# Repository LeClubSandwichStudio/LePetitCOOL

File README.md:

# Le Petit COOL
The Open Source DIY Greenhouse Kit for Makers

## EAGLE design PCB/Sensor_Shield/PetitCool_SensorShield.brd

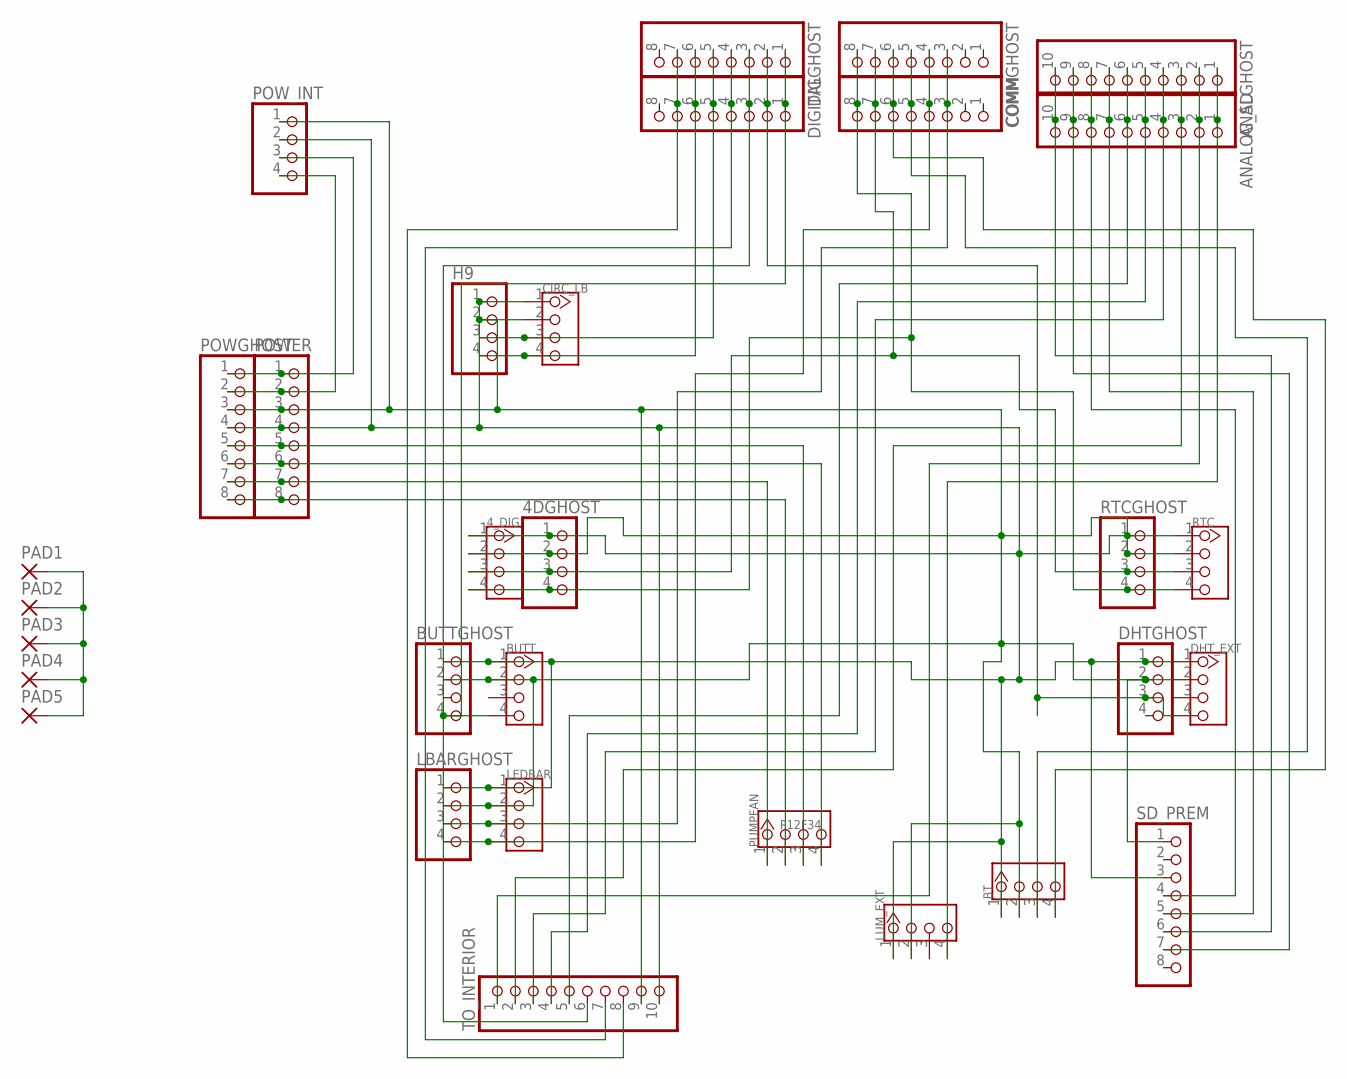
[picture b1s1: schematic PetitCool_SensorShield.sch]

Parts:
4DGHOST: PINHD-1X4; 1X04
4_DIG: TWIG-4P-2.0-2.0; 4P-2.0
ANALGHOST: PINHD-1X10; 1X10
ANALOG_SD: PINHD-1X10; 1X10
BT: TWIG-4P-2.0-2.0; 4P-2.0
BUTT: TWIG-4P-2.0-2.0; 4P-2.0
BUTTGHOST: PINHD-1X4; 1X04
CIRC_LB: TWIG-4P-2.0-2.0; 4P-2.0
COMM: PINHD-1X8; 1X08
COMMGHOST: PINHD-1X8; 1X08
DHTGHOST: PINHD-1X4; 1X04
DHT_EXT: TWIG-4P-2.0-2.0; 4P-2.0
DIGGHOST: PINHD-1X8; 1X08
DIGITAL: PINHD-1X8; 1X08
H9: PINHD-1X4; 1X04
LBARGHOST: PINHD-1X4; 1X04
LEDBAR: TWIG-4P-2.0-2.0; 4P-2.0
LUM_EXT: TWIG-4P-2.0-2.0; 4P-2.0
PAD1, PAD2, PAD3, PAD4, PAD5: 2,15/1,0
POWER: PINHD-1X8; 1X08
POWGHOST: PINHD-1X8; 1X08
POW_INT: PINHD-1X4; 1X04
PUMPFAN: P12F34; 4P-2.0
RTC: TWIG-4P-2.0-2.0; 4P-2.0
RTCGHOST: PINHD-1X4; 1X04
SD_PREM: PINHD-1X8; 1X08
TO_INTERIOR: PINHD-1X10; 1X10

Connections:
+5V: 4DGHOST.2, 4_DIG.2, BT.2, BUTT.2, BUTTGHOST.2, CIRC_LB.2, DHTGHOST.2, DHT_EXT.2, H9.2, LBARGHOST.2, LEDBAR.2, LUM_EXT.2, POWER.3, POWGHOST.3, POW_INT.1, RTC.2, RTCGHOST.2, SD_PREM.1, TO_INTERIOR.9
+12V: POWER.1, POWGHOST.1, POW_INT.3
+FANS: POWER.5, POWGHOST.5, PUMPFAN.3
+PUMP: POWER.7, POWGHOST.7, PUMPFAN.1
A_PTSHIELD(A14): ANALGHOST.6, ANALOG_SD.6, TO_INTERIOR.5
BT_RX: BT.3, COMM.5, COMMGHOST.5
BT_TX: BT.4, COMM.6, COMMGHOST.6
BUTT(32): BUTT.4, BUTTGHOST.4, DIGGHOST.1, DIGITAL.1
CLB_CLK(42): CIRC_LB.4, DIGGHOST.6, DIGITAL.6, H9.4
CLB_DATA(40): CIRC_LB.3, DIGGHOST.5, DIGITAL.5, H9.3
DHT_EXT(34): DHTGHOST.3, DHT_EXT.4, DIGGHOST.2, DIGITAL.2
DHT_INT(36): DIGGHOST.3, DIGITAL.3, TO_INTERIOR.6
D_PTSHIELD(44): DIGGHOST.7, DIGITAL.7, TO_INTERIOR.8
GND_5V: 4DGHOST.1, 4_DIG.1, BT.1, BUTT.1, BUTTGHOST.1, CIRC_LB.1, DHTGHOST.1, DHT_EXT.1, H9.1, LBARGHOST.1, LEDBAR.1, LUM_EXT.1, PAD1.1, PAD2.1, PAD3.1, PAD4.1, PAD5.1, POWER.4, POWGHOST.4, POW_INT.2, RTC.1, RTCGHOST.1, SD_PREM.3, TO_INTERIOR.10
GND_12V: POWER.2, POWGHOST.2, POW_INT.4
GND_FANS: POWER.6, POWGHOST.6, PUMPFAN.4
GND_PUMP: POWER.8, POWGHOST.8, PUMPFAN.2
LEDBAR_RX: COMM.3, COMMGHOST.3, LBARGHOST.3, LEDBAR.3
LEDBAR_TX: COMM.4, COMMGHOST.4, LBARGHOST.4, LEDBAR.4
LUM_EXT(A9): ANALGHOST.1, ANALOG_SD.1, LUM_EXT.4
LUM_INT(A10): ANALGHOST.2, ANALOG_SD.2, TO_INTERIOR.1
MOIST_1(A11): ANALGHOST.3, ANALOG_SD.3, TO_INTERIOR.2
MOIST_2(A12): ANALGHOST.4, ANALOG_SD.4, TO_INTERIOR.3
MOIST_3(A13): ANALGHOST.5, ANALOG_SD.5, TO_INTERIOR.4
PROXI_US(38): DIGGHOST.4, DIGITAL.4, TO_INTERIOR.7
SCL: 4DGHOST.4, 4_DIG.4, COMM.8, COMMGHOST.8, RTC.4, RTCGHOST.4
SDA: 4DGHOST.3, 4_DIG.3, COMM.7, COMMGHOST.7, RTC.3, RTCGHOST.3
SD_CLK(52): ANALGHOST.8, ANALOG_SD.8, SD_PREM.4
SD_CS(53): ANALGHOST.9, ANALOG_SD.9, SD_PREM.7
SD_DI(51): ANALGHOST.10, ANALOG_SD.10, SD_PREM.6
SD_DO(50): ANALGHOST.7, ANALOG_SD.7, SD_PREM.5

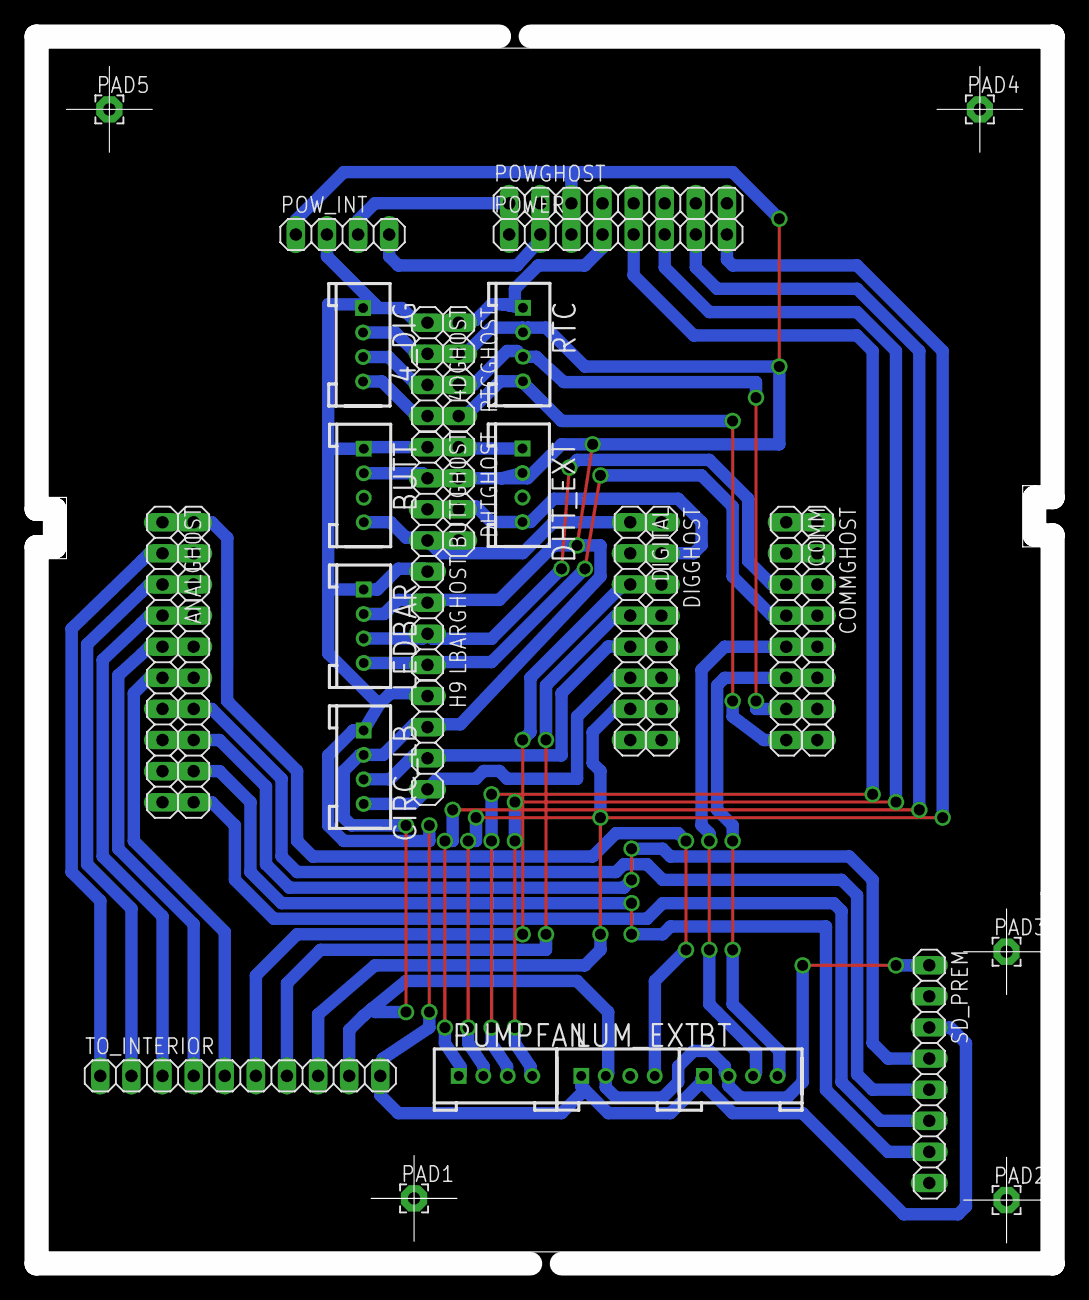
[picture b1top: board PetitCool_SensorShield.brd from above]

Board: 2 copper layers, 83.0 x 100.2 mm, 31 parts (0 on the bottom side), 31 nets.

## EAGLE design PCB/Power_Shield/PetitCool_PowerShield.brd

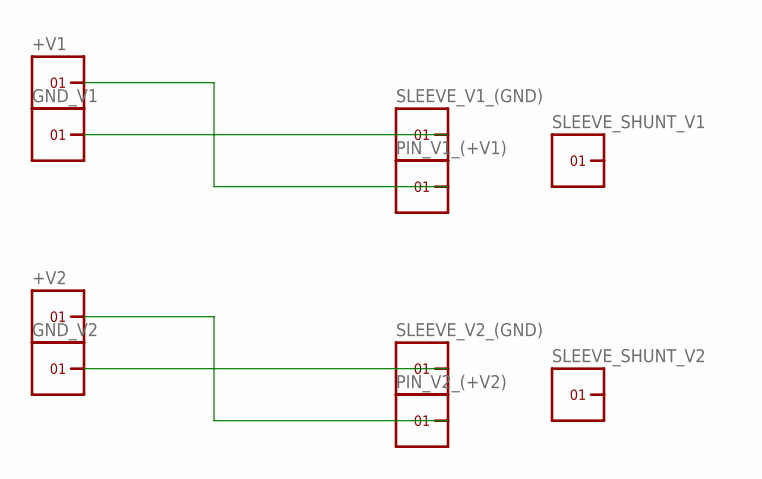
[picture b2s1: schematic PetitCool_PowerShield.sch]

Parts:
+V1, +V2: 1X1
GND_V1, GND_V2: 1X1
PIN_V1_(+V1), PIN_V2_(+V2): 1X1
SLEEVE_SHUNT_V1, SLEEVE_SHUNT_V2: 1X1
SLEEVE_V1_(GND), SLEEVE_V2_(GND): 1X1

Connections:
+V1: +V1.1, PIN_V1_(+V1).1
+V2: +V2.1, PIN_V2_(+V2).1
GND_V1: GND_V1.1, SLEEVE_V1_(GND).1
GND_V2: GND_V2.1, SLEEVE_V2_(GND).1

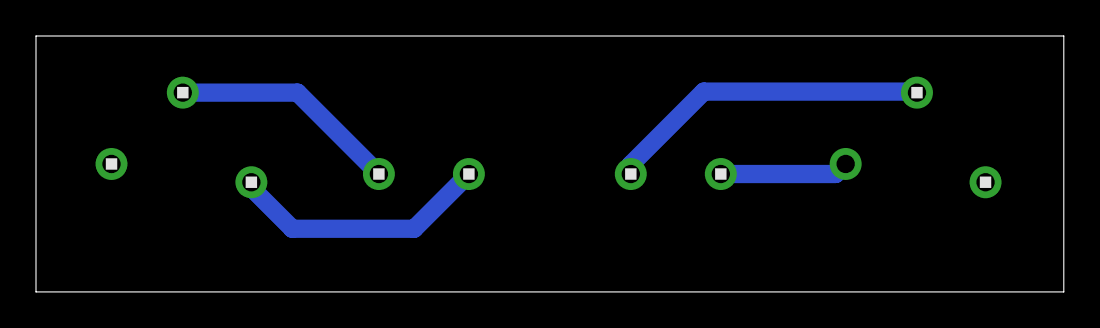
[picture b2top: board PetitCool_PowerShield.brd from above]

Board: 2 copper layers, 57.1 x 14.2 mm, 10 parts (1 on the bottom side), 4 nets.

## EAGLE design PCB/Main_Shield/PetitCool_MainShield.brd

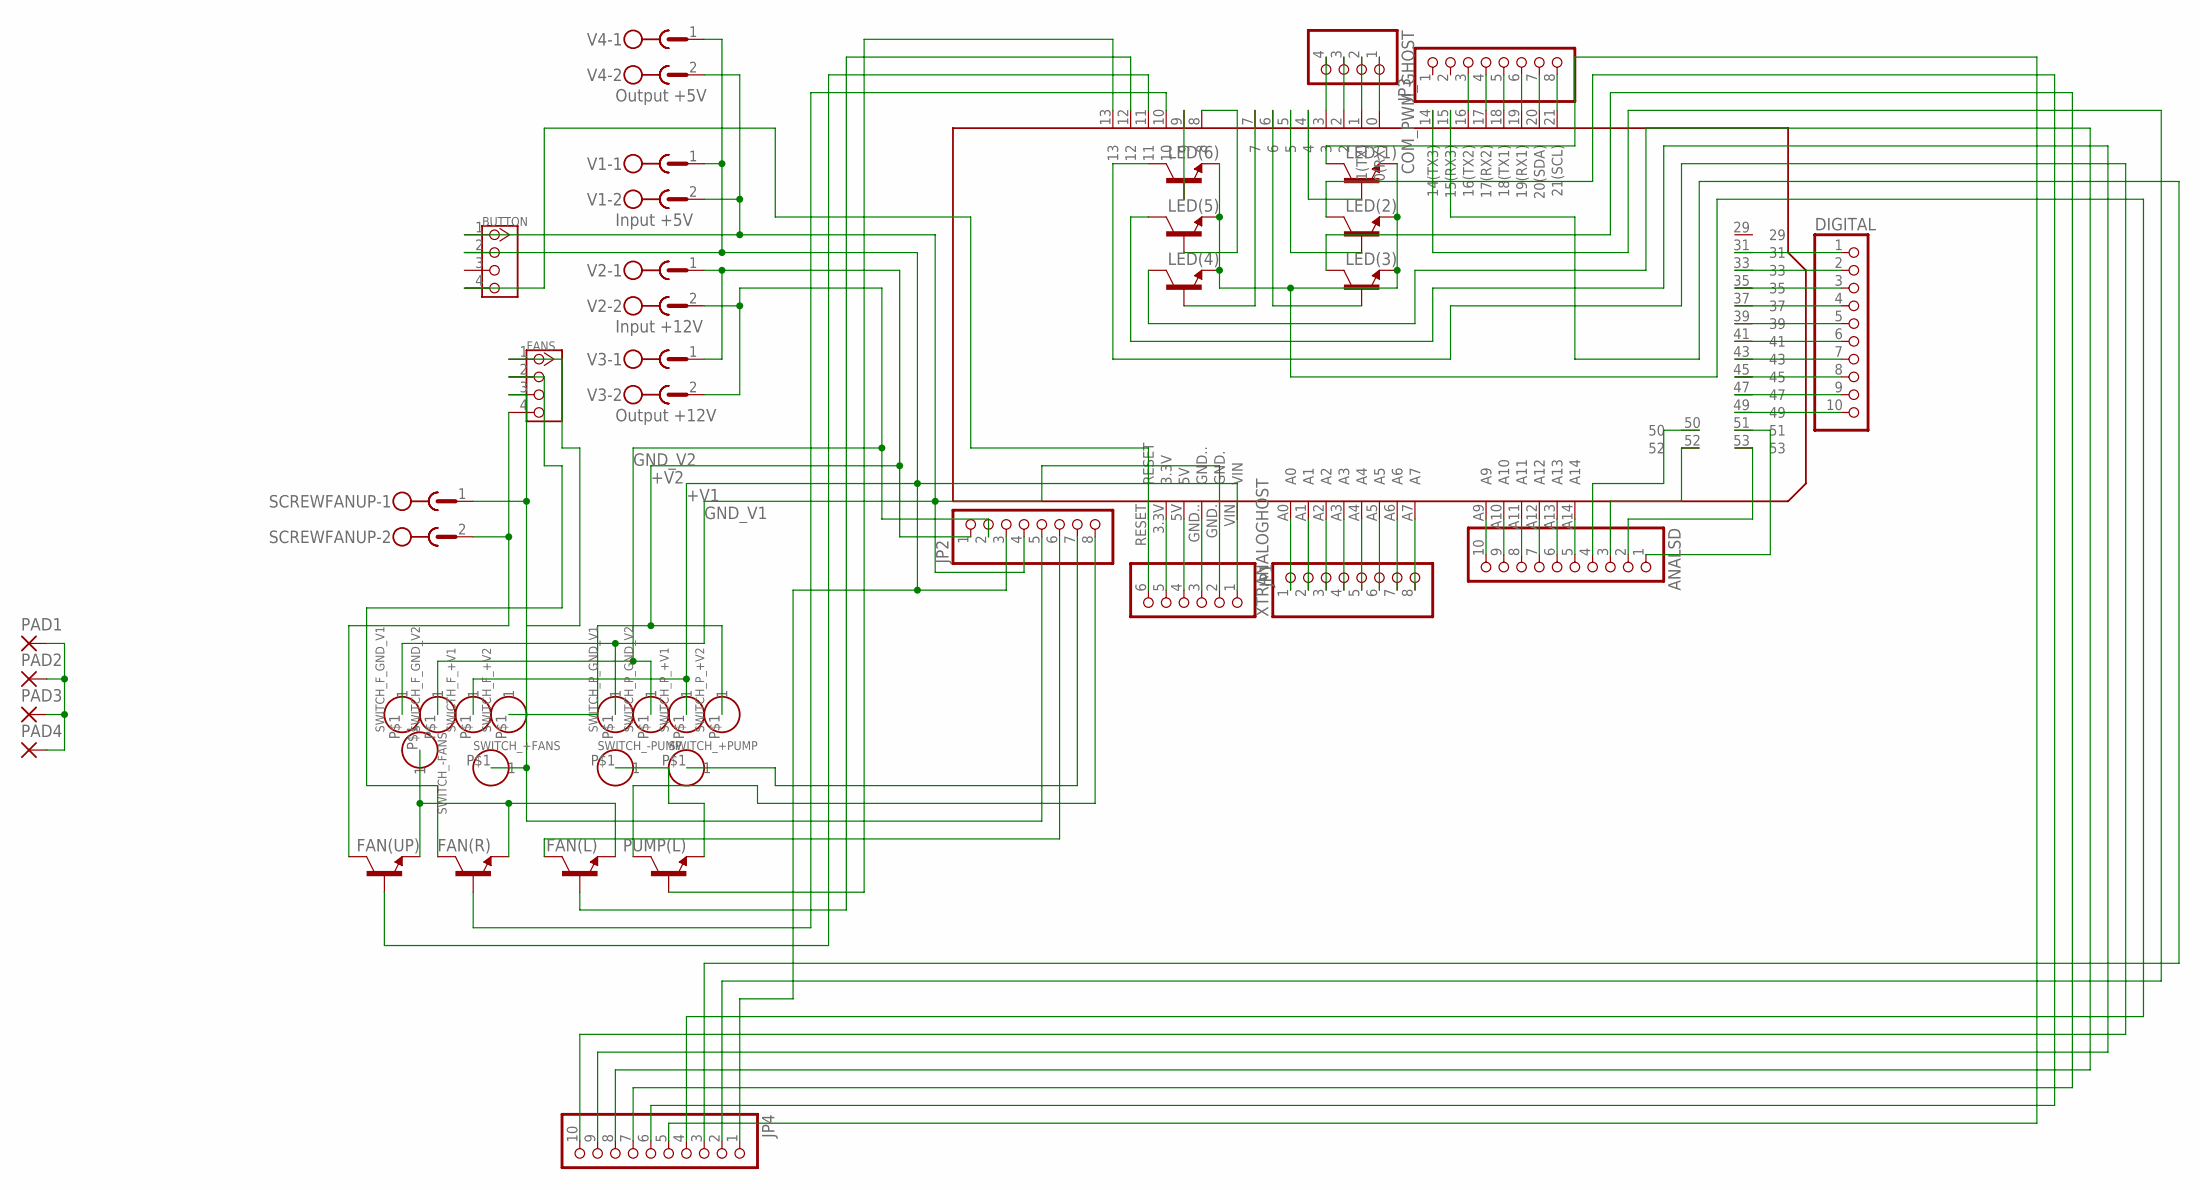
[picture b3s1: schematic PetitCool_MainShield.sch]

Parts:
ANALSD: PINHD-1X10; 1X10
BUTTON: TWIG-4P-2.0-2.0; 4P-2.0
COM_PWM_GHOST: PINHD-1X4; 1X04
DIGITAL: PINHD-1X10; 1X10
FAN(L): DAR500
FAN(R): DAR500
FAN(UP): DAR500
FANS: TWIG-4P-2.0-2.0; 4P-2.0
JP1: PINHD-1X6; 1X06
JP2, JP3: PINHD-1X8; 1X08
JP4: PINHD-1X10; 1X10
LED(1), LED(2), LED(3), LED(4), LED(5), LED(6): DAR500
PAD1, PAD2, PAD3, PAD4: 2,15/1,0
PCB1: SHIELD_MEGA
PUMP(L): DAR500
SCREWFANUP: MSTBV2
SWICTH_F_+V1: HEADER-1P-70; 1P-100/70MIL
SWITCH_+FANS: HEADER-1P-70; 1P-100/70MIL
SWITCH_+PUMP: HEADER-1P-70; 1P-100/70MIL
SWITCH_-FANS: HEADER-1P-70; 1P-100/70MIL
SWITCH_-PUMP: HEADER-1P-70; 1P-100/70MIL
SWITCH_F_+V2: HEADER-1P-70; 1P-100/70MIL
SWITCH_F_GND_V1, SWITCH_F_GND_V2: HEADER-1P-70; 1P-100/70MIL
SWITCH_P_+V1, SWITCH_P_+V2: HEADER-1P-70; 1P-100/70MIL
SWITCH_P_GND_V1, SWITCH_P_GND_V2: HEADER-1P-70; 1P-100/70MIL
V1: Input +5V; MSTBV2
V2: Input +12V; MSTBV2
V3: Output +12V; MSTBV2
V4: Output +5V; MSTBV2
XTRANALOGHOST: PINHD-1X8; 1X08

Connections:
+FAN(UP/R/L): FANS.1, FANS.3, JP2.5, SCREWFANUP.1, SWITCH_+FANS.P$1
+PUMP: JP2.7, SWITCH_+PUMP.P$1
+V1: BUTTON.2, JP1.1, JP2.3, JP4.1, PCB1.VIN, SWICTH_F_+V1.P$1, SWITCH_P_+V1.P$1, V1.1, V4.1
+V2: JP2.1, SWITCH_F_+V2.P$1, SWITCH_P_+V2.P$1, V2.1, V3.1
-FAN(L): FAN(L).1 (C), JP2.6
-FAN(R): FAN(R).1 (C), FANS.2
-FAN(UP): FAN(UP).1 (C), FANS.4, SCREWFANUP.2
-FANS: FAN(L).3 (E), FAN(R).3 (E), FAN(UP).3 (E), SWITCH_-FANS.P$1
-LED(1): JP4.5, LED(1).1 (C)
-LED(2): JP4.6, LED(2).1 (C)
-LED(3): JP4.7, LED(3).1 (C)
-LED(4): JP4.8, LED(4).1 (C)
-LED(5): JP4.9, LED(5).1 (C)
-LED(6): JP4.10, LED(6).1 (C)
-LEDS: JP4.4, LED(1).3 (E), LED(2).3 (E), LED(3).3 (E), LED(4).3 (E), LED(5).3 (E), LED(6).3 (E)
-PUMP: PUMP(L).3 (E), SWITCH_-PUMP.P$1
-PUMP(L): JP2.8, PUMP(L).1 (C)
CAM(RX): JP4.3, PCB1.15 (15(RX3))
CAM(TX): JP4.2, PCB1.14 (14(TX3))
CTRL_FAN(L): FAN(L).2 (B), PCB1.12
CTRL_FAN(R): FAN(R).2 (B), PCB1.10
CTRL_FAN(UP): FAN(UP).2 (B), PCB1.11
CTRL_PUMP: PCB1.13, PUMP(L).2 (B)
GND_V1: BUTTON.1, JP1.2, JP2.4, PAD1.1, PAD2.1, PAD3.1, PAD4.1, PCB1.GND., SWITCH_F_GND_V1.P$1, SWITCH_P_GND_V1.P$1, V1.2, V4.2
GND_V2: JP2.2, SWITCH_F_GND_V2.P$1, SWITCH_P_GND_V2.P$1, V2.2, V3.2
unnamed: ANALSD.3, PCB1.52
unnamed: ANALSD.2, PCB1.53
unnamed: ANALSD.1, PCB1.51
unnamed: JP1.5, PCB1.3.3V
unnamed: JP1.4, PCB1.5V
unnamed: JP1.3, PCB1.GND..
unnamed: COM_PWM_GHOST.1, PCB1.0 (0(RX))
unnamed: COM_PWM_GHOST.2, PCB1.1 (1(TX))
unnamed: COM_PWM_GHOST.3, PCB1.2
unnamed: COM_PWM_GHOST.4, PCB1.3
unnamed: ANALSD.10, PCB1.A9
unnamed: ANALSD.9, PCB1.A10
unnamed: ANALSD.8, PCB1.A11
unnamed: ANALSD.7, PCB1.A12
unnamed: ANALSD.6, PCB1.A13
unnamed: ANALSD.5, PCB1.A14
unnamed: LED(1).2 (B), PCB1.4
unnamed: DIGITAL.1, PCB1.31
unnamed: DIGITAL.2, PCB1.33
unnamed: DIGITAL.3, PCB1.35
unnamed: DIGITAL.4, PCB1.37
unnamed: DIGITAL.5, PCB1.39
unnamed: DIGITAL.6, PCB1.41
unnamed: DIGITAL.7, PCB1.43
unnamed: DIGITAL.8, PCB1.45
unnamed: DIGITAL.9, PCB1.47
unnamed: DIGITAL.10, PCB1.49
unnamed: PCB1.A0, XTRANALOGHOST.1
unnamed: PCB1.A1, XTRANALOGHOST.2
unnamed: PCB1.A2, XTRANALOGHOST.3
unnamed: ANALSD.4, PCB1.50
unnamed: PCB1.A3, XTRANALOGHOST.4
unnamed: PCB1.A4, XTRANALOGHOST.5
unnamed: PCB1.A5, XTRANALOGHOST.6
unnamed: LED(2).2 (B), PCB1.5
unnamed: LED(3).2 (B), PCB1.6
unnamed: LED(4).2 (B), PCB1.7
unnamed: LED(5).2 (B), PCB1.8
unnamed: LED(6).2 (B), PCB1.9
unnamed: PCB1.A6, XTRANALOGHOST.7
unnamed: PCB1.A7, XTRANALOGHOST.8
RESET: BUTTON.4, JP1.6, PCB1.RESET
RX_BT: JP3.4, PCB1.17 (17(RX2))
RX_LEDBAR: JP3.6, PCB1.19 (19(RX1))
SCL_(RTC+4D): JP3.8, PCB1.21 (21(SCL))
SDA_(RTC+4D): JP3.7, PCB1.20 (20(SDA))
TX_BT: JP3.3, PCB1.16 (16(TX2))
TX_LEDBAR: JP3.5, PCB1.18 (18(TX1))

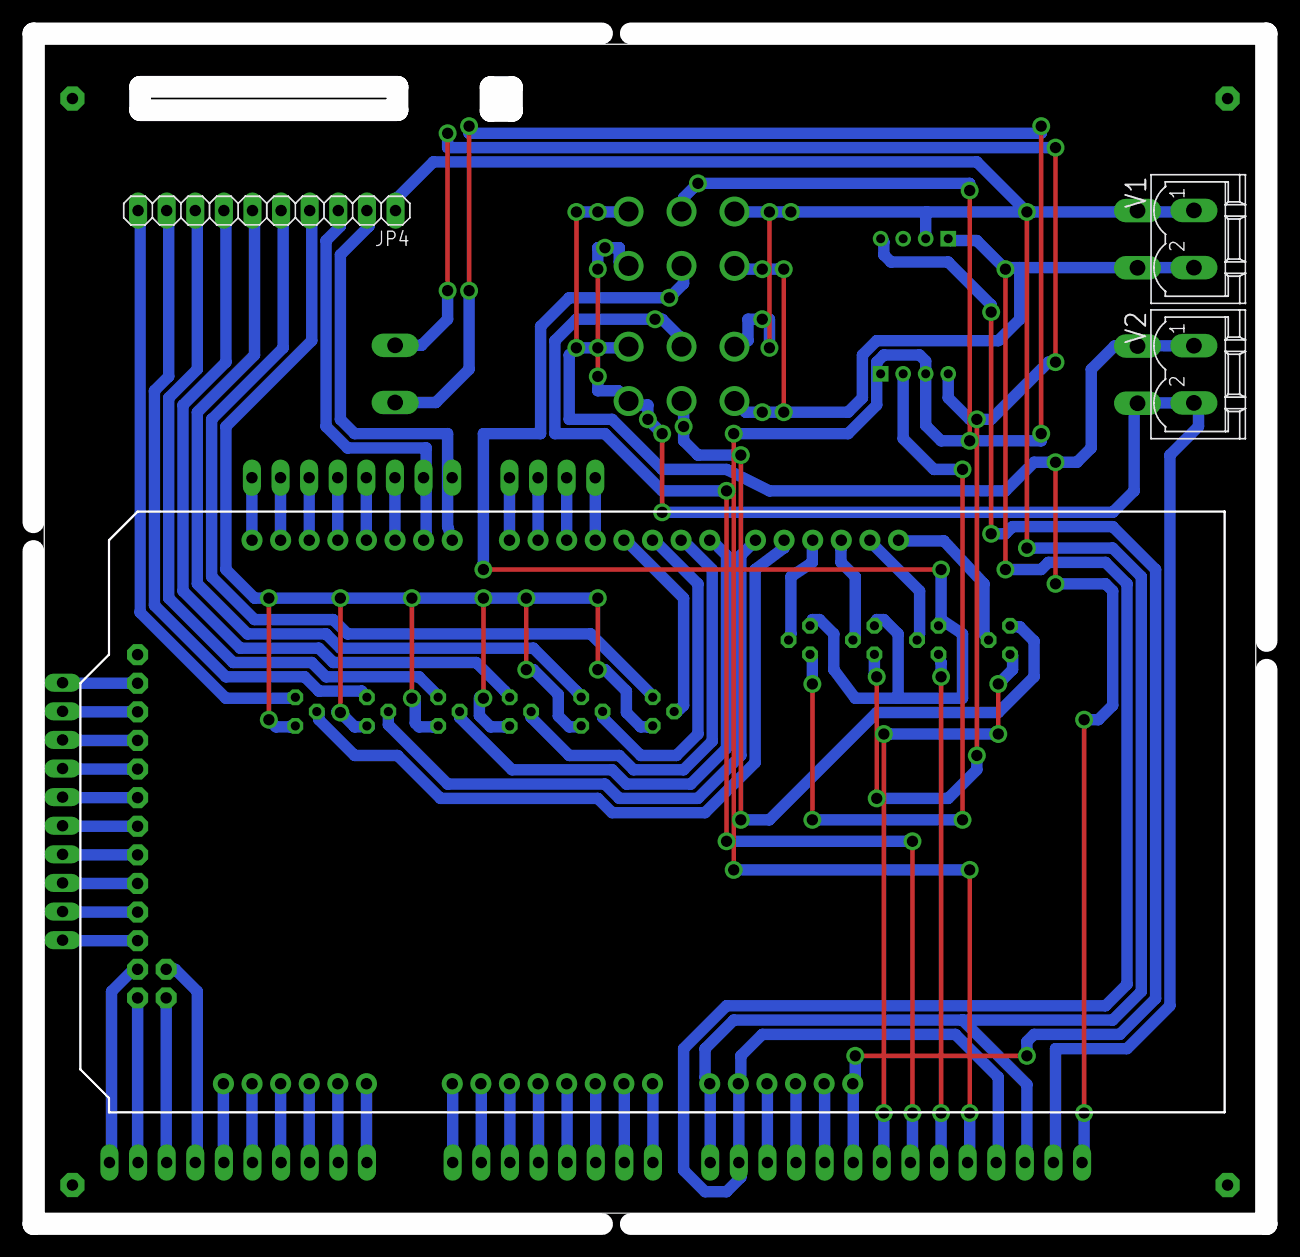
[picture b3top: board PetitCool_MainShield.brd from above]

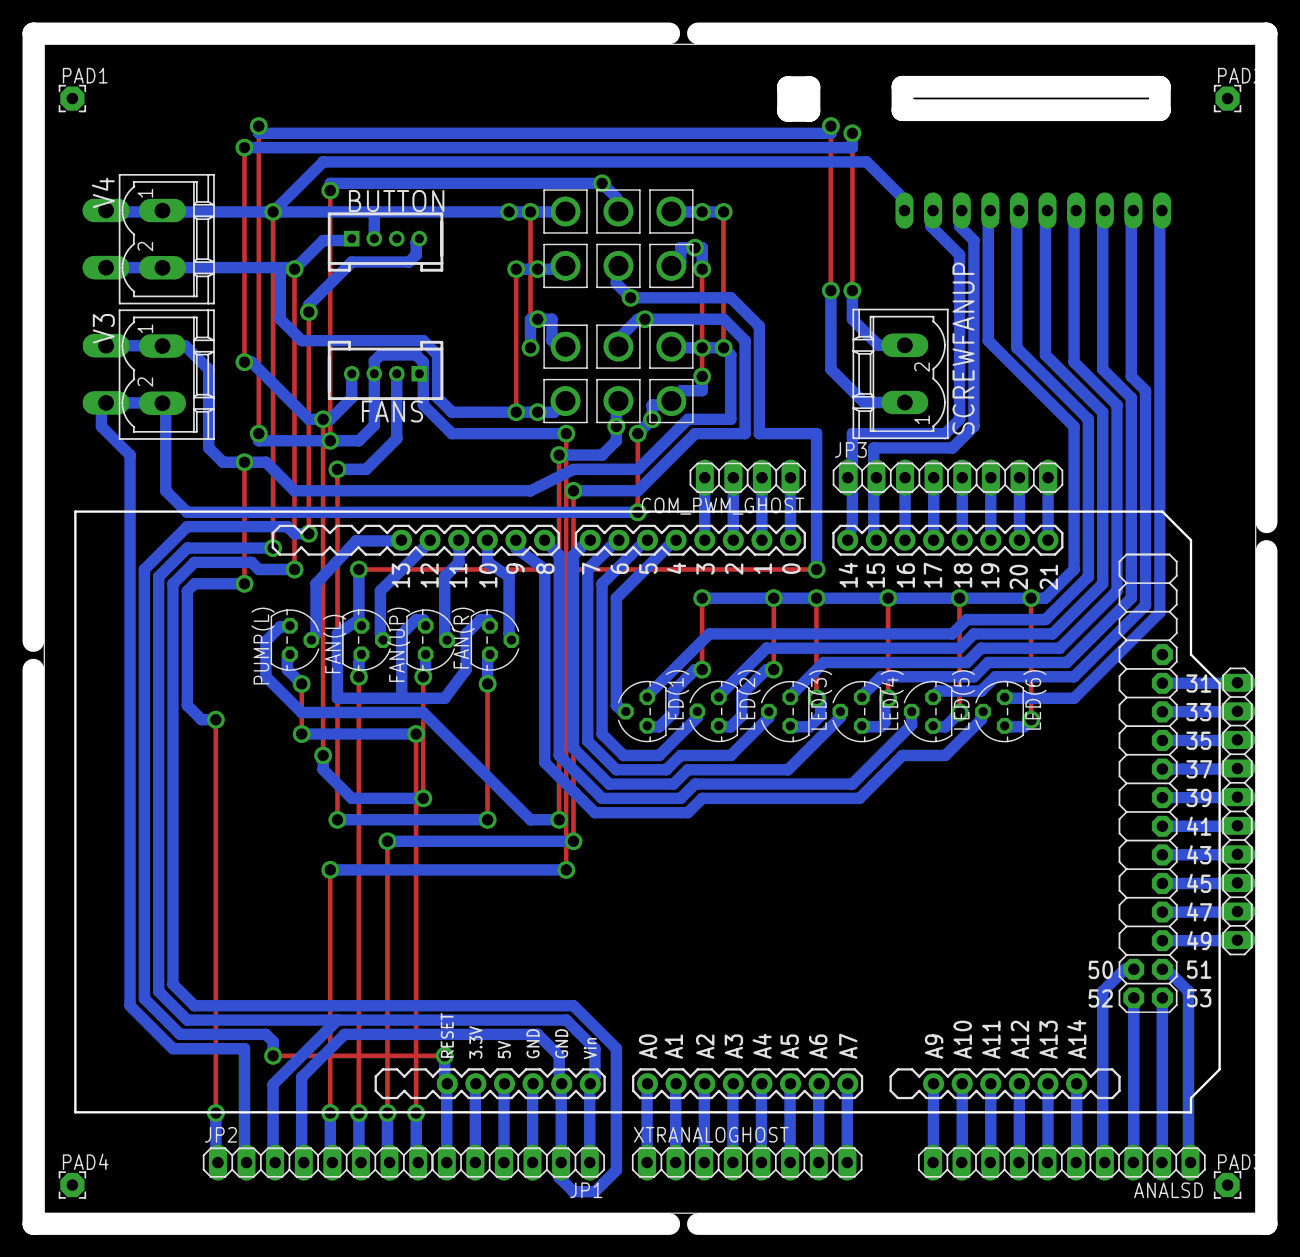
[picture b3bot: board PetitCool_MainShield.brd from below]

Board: 1 copper layer, 109.5 x 105.7 mm, 42 parts (39 on the bottom side), 73 nets.

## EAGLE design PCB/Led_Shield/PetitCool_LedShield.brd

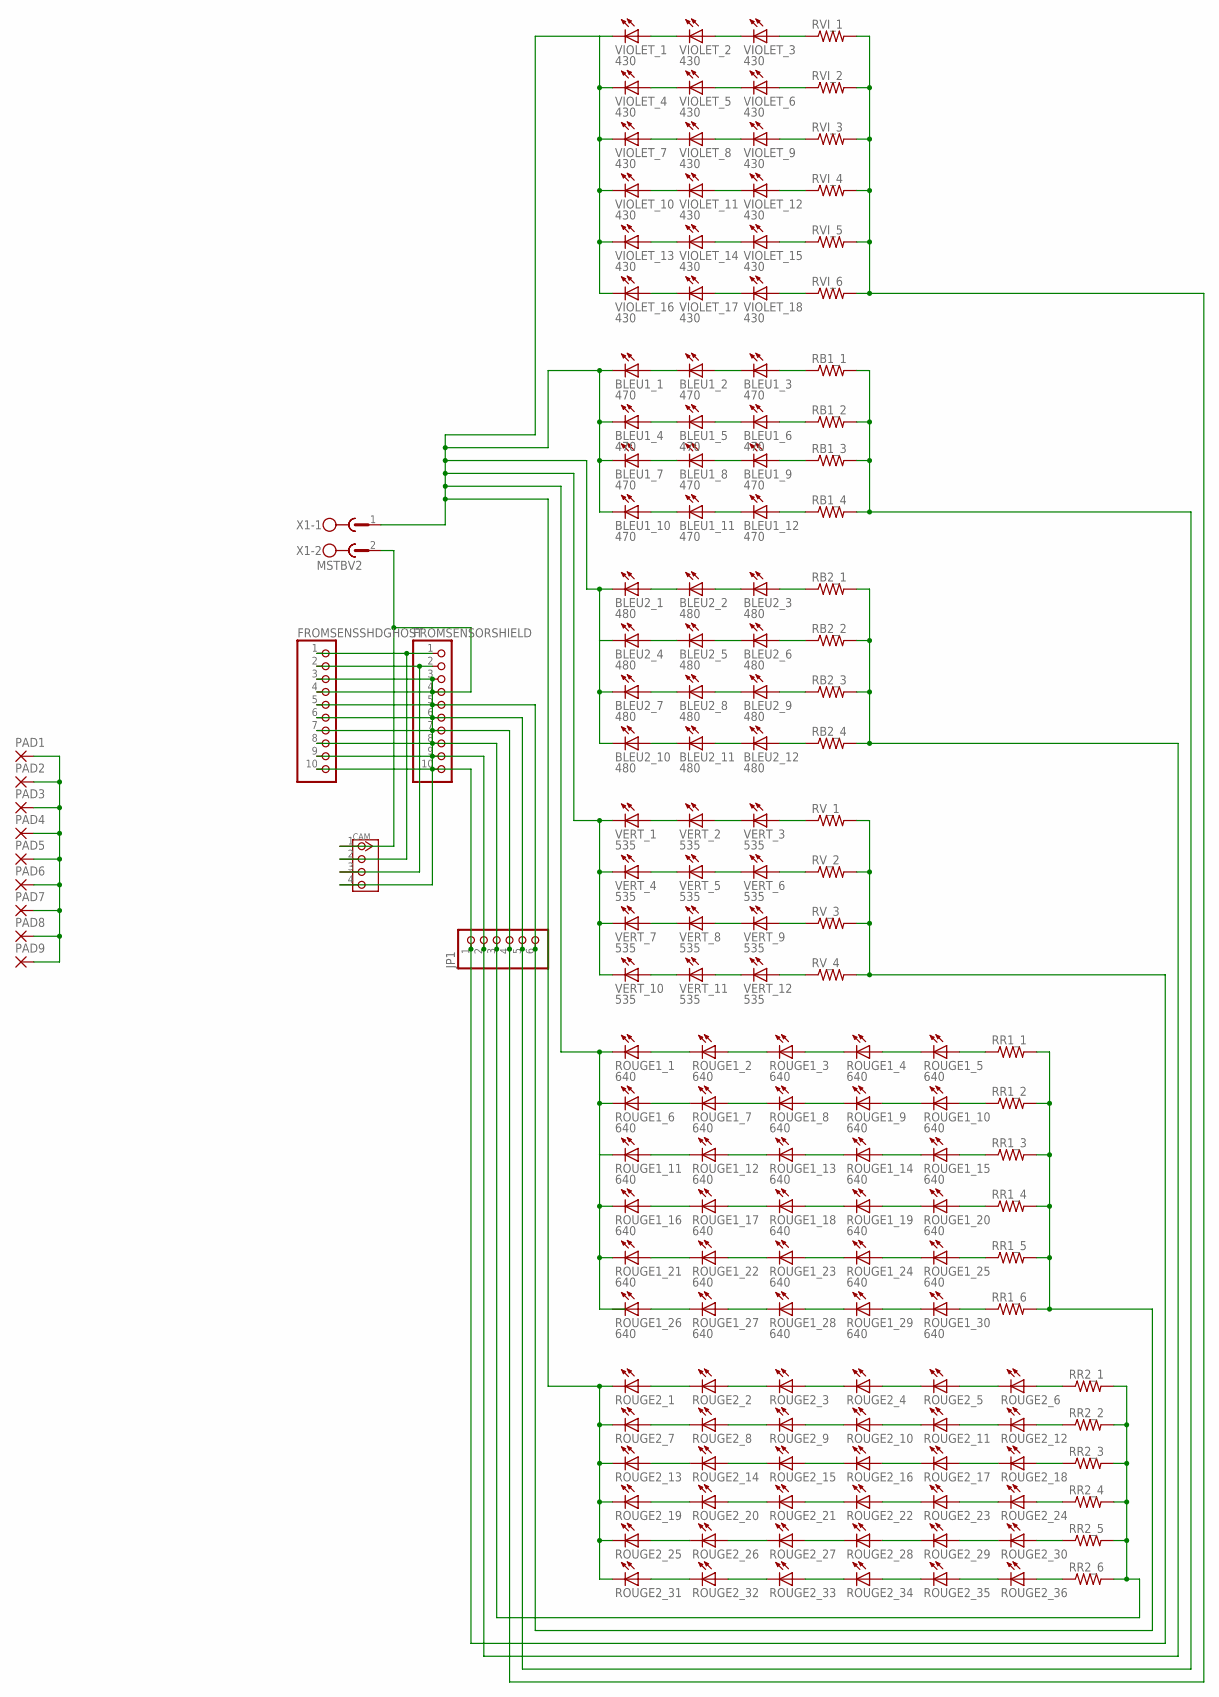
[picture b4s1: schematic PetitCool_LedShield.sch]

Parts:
BLEU1_1, BLEU1_2, BLEU1_3, BLEU1_4, BLEU1_5, BLEU1_6, BLEU1_7, BLEU1_8, BLEU1_9, BLEU1_10, BLEU1_11, BLEU1_12: 470; LED5MM
BLEU2_1, BLEU2_2, BLEU2_3, BLEU2_4, BLEU2_5, BLEU2_6, BLEU2_7, BLEU2_8, BLEU2_9, BLEU2_10, BLEU2_11, BLEU2_12: 480; LED5MM
CAM: TWIG-4P-2.0-2.0; 4P-2.0
FROMSENSORSHIELD: PINHD-1X10; 1X10
FROMSENSSHDGHOST: PINHD-1X10; 1X10
JP1: PINHD-1X6; 1X06
PAD1, PAD2, PAD3, PAD4, PAD5, PAD6, PAD7, PAD8, PAD9: 2,15/1,0
RB1_1, RB1_2, RB1_3, RB1_4, RB2_1, RB2_2, RB2_3, RB2_4: R-US_0204/7; 0204/7
ROUGE1_1, ROUGE1_2, ROUGE1_3, ROUGE1_4, ROUGE1_5, ROUGE1_6, ROUGE1_7, ROUGE1_8, ROUGE1_9, ROUGE1_10, ROUGE1_11, ROUGE1_12, ROUGE1_13, ROUGE1_14, ROUGE1_15, ROUGE1_16, ROUGE1_17, ROUGE1_18, ROUGE1_19, ROUGE1_20, ROUGE1_21, ROUGE1_22, ROUGE1_23, ROUGE1_24, ROUGE1_25, ROUGE1_26, ROUGE1_27, ROUGE1_28, ROUGE1_29, ROUGE1_30: 640; LED5MM
ROUGE2_1, ROUGE2_2, ROUGE2_3, ROUGE2_4, ROUGE2_5, ROUGE2_6, ROUGE2_7, ROUGE2_8, ROUGE2_9, ROUGE2_10, ROUGE2_11, ROUGE2_12, ROUGE2_13, ROUGE2_14, ROUGE2_15, ROUGE2_16, ROUGE2_17, ROUGE2_18, ROUGE2_19, ROUGE2_20, ROUGE2_21, ROUGE2_22, ROUGE2_23, ROUGE2_24, ROUGE2_25, ROUGE2_26, ROUGE2_27, ROUGE2_28, ROUGE2_29, ROUGE2_30, ROUGE2_31, ROUGE2_32, ROUGE2_33, ROUGE2_34, ROUGE2_35, ROUGE2_36: LED5MM
RR1_1, RR1_2, RR1_3, RR1_4, RR1_5, RR1_6, RR2_1, RR2_2, RR2_3, RR2_4, RR2_5, RR2_6: R-US_0204/7; 0204/7
RVI_1, RVI_2, RVI_3, RVI_4, RVI_5, RVI_6: R-US_0204/7; 0204/7
RV_1, RV_2, RV_3, RV_4: R-US_0204/7; 0204/7
VERT_1, VERT_2, VERT_3, VERT_4, VERT_5, VERT_6, VERT_7, VERT_8, VERT_9, VERT_10, VERT_11, VERT_12: 535; LED5MM
VIOLET_1, VIOLET_2, VIOLET_3, VIOLET_4, VIOLET_5, VIOLET_6, VIOLET_7, VIOLET_8, VIOLET_9, VIOLET_10, VIOLET_11, VIOLET_12, VIOLET_13, VIOLET_14, VIOLET_15, VIOLET_16, VIOLET_17, VIOLET_18: 430; LED5MM
X1: MSTBV2

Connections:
+5V: CAM.2, FROMSENSORSHIELD.1, FROMSENSSHDGHOST.1
+12V: BLEU1_1.K (C), BLEU1_4.K (C), BLEU1_7.K (C), BLEU1_10.K (C), BLEU2_1.K (C), BLEU2_4.K (C), BLEU2_7.K (C), BLEU2_10.K (C), ROUGE1_1.K (C), ROUGE1_6.K (C), ROUGE1_11.K (C), ROUGE1_16.K (C), ROUGE1_21.K (C), ROUGE2_1.K (C), ROUGE2_7.K (C), ROUGE2_13.K (C), ROUGE2_19.K (C), ROUGE2_25.K (C), ROUGE2_31.K (C), VERT_1.K (C), VERT_4.K (C), VERT_7.K (C), VERT_10.K (C), VIOLET_1.K (C), VIOLET_4.K (C), VIOLET_7.K (C), VIOLET_10.K (C), VIOLET_13.K (C), VIOLET_16.K (C), X1.1
-LED1: FROMSENSORSHIELD.8, FROMSENSSHDGHOST.8, JP1.3, RR2_1.2, RR2_2.2, RR2_3.2, RR2_4.2, RR2_5.2, RR2_6.2
-LED2: FROMSENSORSHIELD.5, FROMSENSSHDGHOST.5, JP1.6, RR1_1.2, RR1_2.2, RR1_3.2, RR1_4.2, RR1_5.2, RR1_6.2
-LED3: FROMSENSORSHIELD.10, FROMSENSSHDGHOST.10, JP1.1, RV_1.2, RV_2.2, RV_3.2, RV_4.2
-LED4: FROMSENSORSHIELD.9, FROMSENSSHDGHOST.9, JP1.2, RB2_1.2, RB2_2.2, RB2_3.2, RB2_4.2
-LED5: FROMSENSORSHIELD.6, FROMSENSSHDGHOST.6, JP1.5, RB1_1.2, RB1_2.2, RB1_3.2, RB1_4.2
-LED6: FROMSENSORSHIELD.7, FROMSENSSHDGHOST.7, JP1.4, RVI_1.2, RVI_2.2, RVI_3.2, RVI_4.2, RVI_5.2, RVI_6.2
CAM_RX: CAM.3, FROMSENSORSHIELD.2, FROMSENSSHDGHOST.2
CAM_TX: CAM.4, FROMSENSORSHIELD.3, FROMSENSSHDGHOST.3
GND_12V: CAM.1, FROMSENSORSHIELD.4, FROMSENSSHDGHOST.4, PAD1.1, PAD2.1, PAD3.1, PAD4.1, PAD5.1, PAD6.1, PAD7.1, PAD8.1, PAD9.1, X1.2
unnamed: ROUGE2_1.A, ROUGE2_2.K (C)
unnamed: ROUGE2_2.A, ROUGE2_3.K (C)
unnamed: ROUGE2_3.A, ROUGE2_4.K (C)
unnamed: ROUGE2_4.A, ROUGE2_5.K (C)
unnamed: ROUGE2_5.A, ROUGE2_6.K (C)
unnamed: ROUGE2_6.A, RR2_1.1
unnamed: ROUGE2_7.A, ROUGE2_8.K (C)
unnamed: ROUGE2_8.A, ROUGE2_9.K (C)
unnamed: ROUGE2_9.A, ROUGE2_10.K (C)
unnamed: ROUGE2_10.A, ROUGE2_11.K (C)
unnamed: ROUGE2_11.A, ROUGE2_12.K (C)
unnamed: ROUGE2_12.A, RR2_2.1
unnamed: ROUGE2_13.A, ROUGE2_14.K (C)
unnamed: ROUGE2_14.A, ROUGE2_15.K (C)
unnamed: ROUGE2_15.A, ROUGE2_16.K (C)
unnamed: ROUGE2_16.A, ROUGE2_17.K (C)
unnamed: ROUGE2_17.A, ROUGE2_18.K (C)
unnamed: ROUGE2_18.A, RR2_3.1
unnamed: ROUGE2_19.A, ROUGE2_20.K (C)
unnamed: ROUGE2_20.A, ROUGE2_21.K (C)
unnamed: ROUGE2_21.A, ROUGE2_22.K (C)
unnamed: ROUGE2_22.A, ROUGE2_23.K (C)
unnamed: ROUGE2_23.A, ROUGE2_24.K (C)
unnamed: ROUGE2_24.A, RR2_4.1
unnamed: ROUGE2_25.A, ROUGE2_26.K (C)
unnamed: ROUGE2_26.A, ROUGE2_27.K (C)
unnamed: ROUGE2_27.A, ROUGE2_28.K (C)
unnamed: ROUGE2_28.A, ROUGE2_29.K (C)
unnamed: ROUGE2_29.A, ROUGE2_30.K (C)
unnamed: ROUGE2_30.A, RR2_5.1
unnamed: ROUGE2_31.A, ROUGE2_32.K (C)
unnamed: ROUGE2_32.A, ROUGE2_33.K (C)
unnamed: ROUGE2_33.A, ROUGE2_34.K (C)
unnamed: ROUGE2_34.A, ROUGE2_35.K (C)
unnamed: ROUGE2_35.A, ROUGE2_36.K (C)
unnamed: ROUGE2_36.A, RR2_6.1
unnamed: ROUGE1_26.A, ROUGE1_27.K (C)
unnamed: ROUGE1_27.A, ROUGE1_28.K (C)
unnamed: ROUGE1_28.A, ROUGE1_29.K (C)
unnamed: ROUGE1_29.A, ROUGE1_30.K (C)
unnamed: ROUGE1_30.A, RR1_6.1
unnamed: ROUGE1_21.A, ROUGE1_22.K (C)
unnamed: ROUGE1_22.A, ROUGE1_23.K (C)
unnamed: ROUGE1_23.A, ROUGE1_24.K (C)
unnamed: ROUGE1_24.A, ROUGE1_25.K (C)
unnamed: ROUGE1_25.A, RR1_5.1
unnamed: ROUGE1_16.A, ROUGE1_17.K (C)
unnamed: ROUGE1_17.A, ROUGE1_18.K (C)
unnamed: ROUGE1_18.A, ROUGE1_19.K (C)
unnamed: ROUGE1_19.A, ROUGE1_20.K (C)
unnamed: ROUGE1_20.A, RR1_4.1
unnamed: ROUGE1_11.A, ROUGE1_12.K (C)
unnamed: ROUGE1_12.A, ROUGE1_13.K (C)
unnamed: ROUGE1_13.A, ROUGE1_14.K (C)
unnamed: ROUGE1_14.A, ROUGE1_15.K (C)
unnamed: ROUGE1_15.A, RR1_3.1
unnamed: ROUGE1_6.A, ROUGE1_7.K (C)
unnamed: ROUGE1_7.A, ROUGE1_8.K (C)
unnamed: ROUGE1_8.A, ROUGE1_9.K (C)
unnamed: ROUGE1_9.A, ROUGE1_10.K (C)
unnamed: ROUGE1_10.A, RR1_2.1
unnamed: ROUGE1_1.A, ROUGE1_2.K (C)
unnamed: ROUGE1_2.A, ROUGE1_3.K (C)
unnamed: ROUGE1_3.A, ROUGE1_4.K (C)
unnamed: ROUGE1_4.A, ROUGE1_5.K (C)
unnamed: ROUGE1_5.A, RR1_1.1
unnamed: VERT_10.A, VERT_11.K (C)
unnamed: VERT_11.A, VERT_12.K (C)
unnamed: RV_4.1, VERT_12.A
unnamed: VERT_7.A, VERT_8.K (C)
unnamed: VERT_8.A, VERT_9.K (C)
unnamed: RV_3.1, VERT_9.A
unnamed: VERT_4.A, VERT_5.K (C)
unnamed: VERT_5.A, VERT_6.K (C)
unnamed: RV_2.1, VERT_6.A
unnamed: VERT_1.A, VERT_2.K (C)
unnamed: VERT_2.A, VERT_3.K (C)
unnamed: RV_1.1, VERT_3.A
unnamed: BLEU2_10.A, BLEU2_11.K (C)
unnamed: BLEU2_11.A, BLEU2_12.K (C)
unnamed: BLEU2_12.A, RB2_4.1
unnamed: BLEU2_7.A, BLEU2_8.K (C)
unnamed: BLEU2_8.A, BLEU2_9.K (C)
unnamed: BLEU2_9.A, RB2_3.1
unnamed: BLEU2_4.A, BLEU2_5.K (C)
unnamed: BLEU2_5.A, BLEU2_6.K (C)
unnamed: BLEU2_6.A, RB2_2.1
unnamed: BLEU2_1.A, BLEU2_2.K (C)
unnamed: BLEU2_2.A, BLEU2_3.K (C)
unnamed: BLEU2_3.A, RB2_1.1
unnamed: BLEU1_10.A, BLEU1_11.K (C)
unnamed: BLEU1_11.A, BLEU1_12.K (C)
unnamed: BLEU1_12.A, RB1_4.1
unnamed: BLEU1_7.A, BLEU1_8.K (C)
unnamed: BLEU1_8.A, BLEU1_9.K (C)
unnamed: BLEU1_9.A, RB1_3.1
unnamed: BLEU1_4.A, BLEU1_5.K (C)
unnamed: BLEU1_5.A, BLEU1_6.K (C)
unnamed: BLEU1_6.A, RB1_2.1
unnamed: BLEU1_1.A, BLEU1_2.K (C)
unnamed: BLEU1_2.A, BLEU1_3.K (C)
unnamed: BLEU1_3.A, RB1_1.1
unnamed: VIOLET_16.A, VIOLET_17.K (C)
unnamed: VIOLET_17.A, VIOLET_18.K (C)
unnamed: RVI_6.1, VIOLET_18.A
unnamed: VIOLET_13.A, VIOLET_14.K (C)
unnamed: VIOLET_14.A, VIOLET_15.K (C)
unnamed: RVI_5.1, VIOLET_15.A
unnamed: VIOLET_10.A, VIOLET_11.K (C)
unnamed: VIOLET_11.A, VIOLET_12.K (C)
unnamed: RVI_4.1, VIOLET_12.A
unnamed: VIOLET_7.A, VIOLET_8.K (C)
unnamed: VIOLET_8.A, VIOLET_9.K (C)
unnamed: RVI_3.1, VIOLET_9.A
unnamed: VIOLET_4.A, VIOLET_5.K (C)
unnamed: VIOLET_5.A, VIOLET_6.K (C)
unnamed: RVI_2.1, VIOLET_6.A
unnamed: VIOLET_1.A, VIOLET_2.K (C)
unnamed: VIOLET_2.A, VIOLET_3.K (C)
unnamed: RVI_1.1, VIOLET_3.A

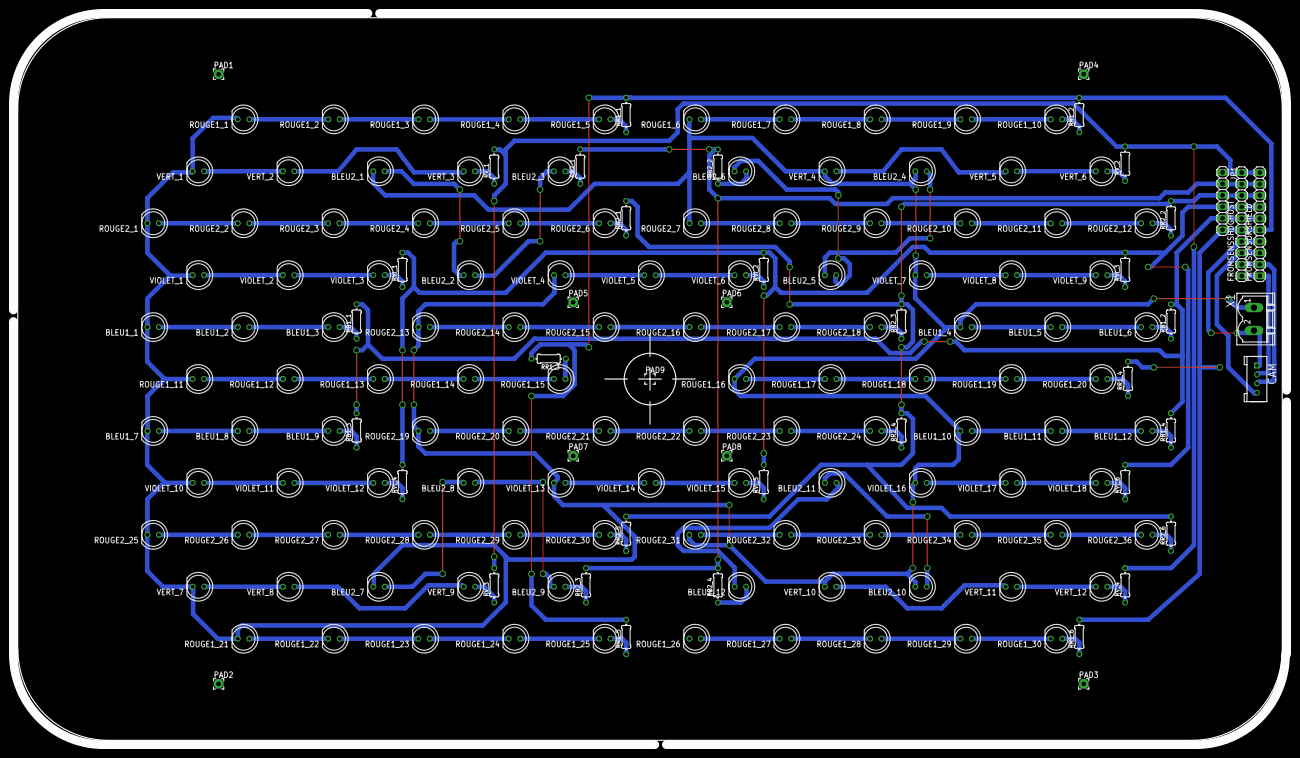
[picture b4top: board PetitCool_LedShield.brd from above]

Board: 2 copper layers, 281.9 x 161.9 mm, 164 parts (0 on the bottom side), 131 nets.
